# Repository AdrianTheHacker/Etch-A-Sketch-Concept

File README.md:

# Etchasketch Concept
This project is designed to be a concept of what an etchasketch could be. It'll allow for modern features that aid artist ability, and truly allow them to *Draw the Future*.

## Requirements
In no particular order, the requirements are as follows:
1. Display has at least 3 colours (white counts as a colour).
2. Display can update at least once per second.
3. Users can control the drawing cursor of the display using rotary inputs which read input a minimum of every 10ms*.
4. The product should be at most 77mm by 100mm by 40mm.
5. Users can save the current drawing on the display on a laptop.
6. Different devices can share a given drawing session to collaborate on designs.

*Note that the rate in which an input is processed is independent of the rate in which the screen will be updating.

## Specifications
* [1] E-Ink display capable of displaying 3 different colours.
* [1] Single button for cycling between colours.
* [2] E-Ink screen uses effective partial updating algorithm for reducing.
* [3] Two potentiometers for reading user inputs.
* [4] PCB has width of 100mm and length of 77mm.
* [5/6] PCB contains a [pre-certified WiFi module](https://www.adafruit.com/product/4201).
* [5/6] Desktop app for managing drawing sessions and saving drawing state.

## Component Selection
Sorted by sub-system.

### Processing
[STM32G4 Hardware Configuration](https://www.st.com/resource/en/application_note/an5093-getting-started-with-stm32g4-series--hardware-development-boards-stmicroelectronics.pdf)
- [2x] [Ceramic capacitor 100nF](https://www.mouser.ca/ProductDetail/TAIYO-YUDEN/MAJCH168BB7104KTEA01?qs=ZcfC38r4PovaTBrG0IdezQ%3D%3D)
- [1x] [Ceramic capacitor 4.7uF](https://www.mouser.ca/ProductDetail/TAIYO-YUDEN/LMK107BJ475KA-T?qs=PzICbMaShUfCoRlxZeLF0g%3D%3D)
- [3x] [Ceramic capacitor 1uF (No CAD Found)](https://www.mouser.ca/ProductDetail/Murata-Electronics/GCM188M8EH105KE08D?qs=ZcfC38r4Posf7JVKT9w1zw%3D%3D)
- [1x] [Ceramic capacitor 10nF](https://www.mouser.ca/ProductDetail/KYOCERA-AVX/06035A103JAT2A?qs=Cw3yY7soYCOJ7MBOLgA8ng%3D%3D)
- [2x] [Ceramic capacitor 6.8pF (No CAD Found)](https://www.mouser.ca/ProductDetail/KYOCERA-AVX/0603YA6R8CAT2A?qs=Q0wCMCRSJ1u%252BWh5kh2d1zQ%3D%3D)
- [2x] [Ceramic capacitor 20pF](https://www.mouser.ca/ProductDetail/KYOCERA-AVX/06031A200KAT2A?qs=vKkcnSRGkVsINiHJTia7rw%3D%3D)
- [1x] [Ferrite beads (No CAD Found)](https://www.mouser.ca/ProductDetail/TE-Connectivity-Sigma-Inductors/BMC-Q1E0000H?qs=IKkN%2F947nfDSkH2nnTPyEw%3D%3D)
- [1x] [Quartz 24MHz (No CAD Found)](https://www.mouser.ca/ProductDetail/KYOCERA-AVX/CX3225FB24000C0FZZH1?qs=Tc%252BHE9vUsnugTp3oEWKKRg%3D%3D)
- [1x] [Quartz 32.764kHz](https://www.mouser.ca/ProductDetail/Vishay-Dale/XT1312HHRXX32K76E?qs=jcD%2FCkGBYeMqyUz9UpSqCw%3D%3D)
- [1x] [Resistor 390Ω](https://www.mouser.ca/ProductDetail/Vishay-Beyschlag/MCT0603MD3900BP500?qs=sGAEpiMZZMtlubZbdhIBIONtIqra%2FA5Yq8ULjaRtKpA%3D)
- [3x] [Resistor 10kΩ](https://www.mouser.ca/ProductDetail/TE-Connectivity-Holsworthy/RA73F1J10KBTDF?qs=sGAEpiMZZMtlubZbdhIBIJBDgjsVQBFl0L0uqFOGEF8%3D)
- [1x] [ST-Link Debugger (STLINK-V3MINIE)](https://www.mouser.ca/ProductDetail/STMicroelectronics/STLINK-V3MINIE?qs=sGAEpiMZZMuqBwn8WqcFUipNgoezRlc4V9M2rz8Us%252BfpLfxQapoDpA%3D%3D)
- [1x] [ST-Link debugger connector (LibraryLoader didn't work)](https://www.digikey.ca/en/products/detail/samtec-inc/FTSH-107-01-F-DV-K/2650001?gclsrc=aw.ds&gad_source=1&gad_campaignid=17336435733&gbraid=0AAAAADrbLlhq2OpxPLWAyTiYmFA62M8dN&gclid=CjwKCAiAuIDJBhBoEiwAxhgyFisN6L1oPr3EJV2HRn68eJmM_TwOISw0mEKeCH2g0jNCqzJe0RDupRoCn4cQAvD_BwE)
- [1x] [STM32G484QET6](https://www.mouser.ca/ProductDetail/STMicroelectronics/STM32G484QET6?qs=uwxL4vQweFOef65amZQ%252BrA%3D%3D)
- [1x] [Switch (No CAD Found)](https://mou.sr/4ixqZ2V)
- [1x] [Pushbutton](https://www.mouser.ca/ProductDetail/CK/PTS125SM73SMTR21M-LFS?qs=t7xnP681wgVp4NpaUUvA%252Bw%3D%3D)

### Power
- [1x] [CR2032 Battery](https://www.mouser.ca/ProductDetail/Murata-Electronics/CR2032?qs=gTYE2QTfZfQ%2FQrgScp89FQ%3D%3D)
- [1x] [CR2032 Connector](https://www.mouser.ca/ProductDetail/Renata/SMTU2032-C?qs=UxeAxwACbqkmlMDdDbz%2FoA%3D%3D)
- [1x] [Power on LED Green](https://www.mouser.ca/ProductDetail/ams-OSRAM/KT-EELP41.12-S2U1-25-2X4X-5-R18?qs=sGAEpiMZZMvVL5Kk7ZYykaXDR74jB6yftoFsk4g727SHxqbUeiiZww%3D%3D)
- [1x] [Resistor 100Ω (for LED) (No CAD Found, Not Requested)](https://www.mouser.ca/ProductDetail/TE-Connectivity-Holsworthy/RT73F1J100RBTD?qs=sGAEpiMZZMtlubZbdhIBIOStsStSd9IEZF4WybNbkN0%3D)
- [1x] [Ceramic capacitor 10uF](https://www.mouser.ca/ProductDetail/KYOCERA-AVX/0603YD106MAT2A?qs=%252BdQmOuGyFcGTGabFXpuZrg%3D%3D)

### Display
[Screen's circuit diagram (Make manually)](https://cdn-shop.adafruit.com/product-files/6393/P6393+C22273-001_datasheet_ZJY296152-0266EABMFGN-R.pdf)
- [1x] [E-Ink display tri-colour 2.66In diagonal](https://www.adafruit.com/product/6393)
- [9x] [Ceramic capacitor 1uF](https://www.mouser.ca/ProductDetail/TAIYO-YUDEN/MAJCT168BB7105KTEA01?qs=ZcfC38r4PotKRnvquyYkSA%3D%3D)
- [1x] [Resistor 2.2Ω (No CAD Found, Not Requested)](https://www.mouser.ca/ProductDetail/Wurth-Elektronik/560112116088?qs=mELouGlnn3eIPFCFgc7e7A%3D%3D)
- [3x] [Diode](https://www.mouser.ca/ProductDetail/onsemi/MBR0530T1G?qs=3JMERSakeboS%2FFOxJUMWeg%3D%3D)
- [1x] [NMOS](https://www.mouser.ca/ProductDetail/Nexperia/NX3008NBKS115?qs=N31o%252Bt096gvSMWdFEcaa8A%3D%3D)
- [1x] [Inductor 47uH (No CAD Found, Not Requested)](https://www.mouser.ca/ProductDetail/Sumida/CDRH2D18-LDNP-470NC?qs=mT6umqgwvA1P4peHEoEcxg%3D%3D)
- [1x] [Screen connector (Downloaded, Add Manually)](https://www.digikey.ca/en/products/detail/w%C3%BCrth-elektronik/687124149022/5047796)

### Controls
- [1x] [Accelerometer](https://www.mouser.ca/ProductDetail/Analog-Devices/ADXL345BCCZ?qs=WIvQP4zGanhoa7YOkGtvEg%3D%3D)
- [1x] [Ceramic capacitor 100nF](https://www.mouser.ca/ProductDetail/TAIYO-YUDEN/MAJCH168BB7104KTEA01?qs=ZcfC38r4PovaTBrG0IdezQ%3D%3D)
- [1x] [Tantalum capacitor 1uF](https://www.mouser.ca/ProductDetail/KYOCERA-AVX/TACL105K010FTA?qs=sGAEpiMZZMtZ1n0r9vR22f0Jgorj1M1u11EugVUWwzY%3D)
- [2x] [Potentiometer 10KΩ (Create Manually)](https://www.adafruit.com/product/3395)
- [2x] [Potentiometer cap](https://www.adafruit.com/product/2057)
- [2x] [Pushbutton](https://www.mouser.ca/ProductDetail/CK/PTS125SM73SMTR21M-LFS?qs=t7xnP681wgVp4NpaUUvA%252Bw%3D%3D)
- [2x] [Resistor 10kΩ](https://www.mouser.ca/ProductDetail/TE-Connectivity-Holsworthy/RA73F1J10KBTDF?qs=sGAEpiMZZMtlubZbdhIBIJBDgjsVQBFl0L0uqFOGEF8%3D)

### Connectivity
- [1x] [WiFi Module (Make Manually, Base off of pin headers)](https://www.adafruit.com/product/4201)
- [3x] [Pin header (Sets of 4)](https://www.mouser.ca/ProductDetail/HARTING/14120416050000?qs=sGAEpiMZZMvlX3nhDDO4ADo1TeYw%2F5hz1M8q0I2khik%3D)

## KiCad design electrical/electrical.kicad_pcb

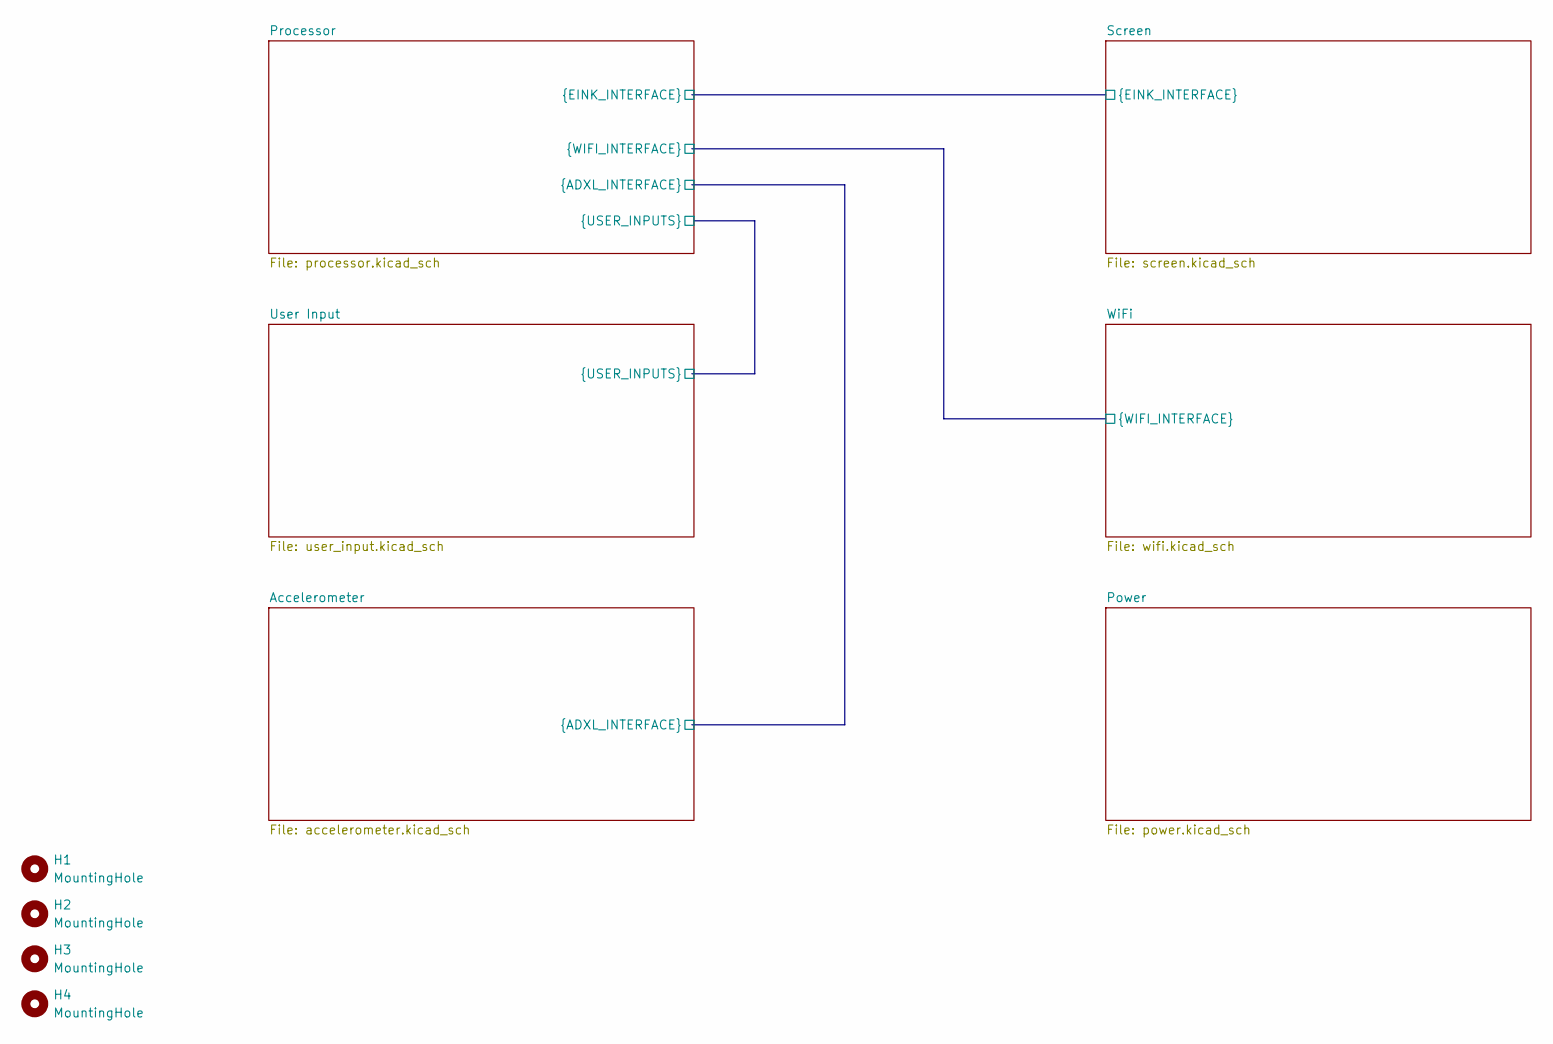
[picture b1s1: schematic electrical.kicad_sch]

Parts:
H1, H2, H3, H4: MountingHole; MountingHole_2.2mm_M2

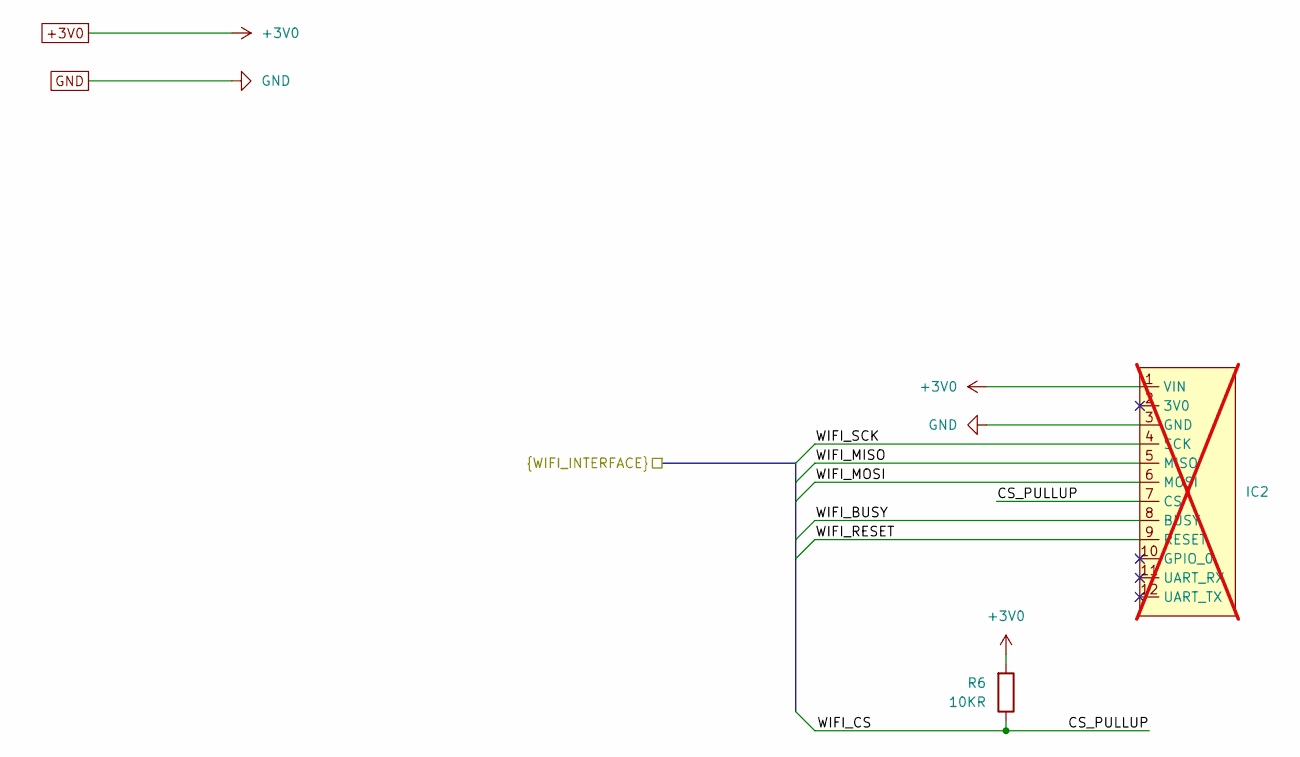
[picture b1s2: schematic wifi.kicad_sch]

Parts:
IC2: THT_WIFI_MODULE; not fitted
R6: 10KR; SMD_RESISTOR_0603

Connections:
+3V0: IC2.1 (VIN), R6.2; also elsewhere on the board
/Processor/WIFI_BUSY: IC2.8 (BUSY); also elsewhere on the board
/Processor/WIFI_CS: IC2.7 (CS), R6.1; also elsewhere on the board
/Processor/WIFI_MISO: IC2.5 (MISO); also elsewhere on the board
/Processor/WIFI_MOSI: IC2.6 (MOSI); also elsewhere on the board
/Processor/WIFI_RESET: IC2.9 (RESET); also elsewhere on the board
/Processor/WIFI_SCK: IC2.4 (SCK); also elsewhere on the board
GND: IC2.3 (GND); also elsewhere on the board

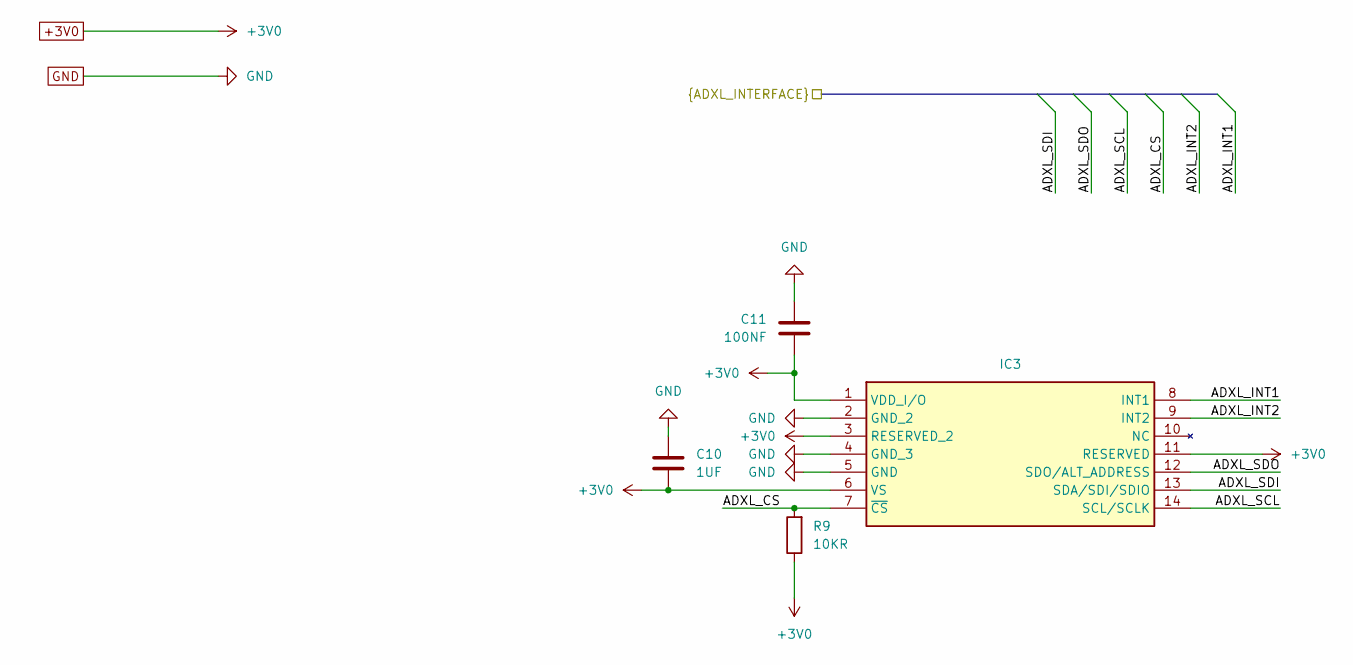
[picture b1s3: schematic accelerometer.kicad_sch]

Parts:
C10: 1UF; SMD_CAPACITOR_TANTALUM_0603_1UF
C11: 100NF; SMD_CAPACITOR_CERAMIC_0603
IC3: SMD_ADXL345BCCZ
R9: 10KR; SMD_RESISTOR_0603

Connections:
+3V0: C10.2, C11.1, IC3.1 (VDD_I/O), IC3.3 (RESERVED_2), IC3.6 (VS), IC3.11 (RESERVED), R9.1; also elsewhere on the board
/Accelerometer/ADXL_CS: IC3.7 (~CS), R9.2; also elsewhere on the board
/Accelerometer/ADXL_INT1: IC3.8 (INT1); also elsewhere on the board
/Accelerometer/ADXL_INT2: IC3.9 (INT2); also elsewhere on the board
/Accelerometer/ADXL_SCL: IC3.14 (SCL/SCLK); also elsewhere on the board
/Accelerometer/ADXL_SDI: IC3.13 (SDA/SDI/SDIO); also elsewhere on the board
/Accelerometer/ADXL_SDO: IC3.12 (SDO/ALT_ADDRESS); also elsewhere on the board
GND: C10.1, C11.2, IC3.2 (GND_2), IC3.4 (GND_3), IC3.5 (GND); also elsewhere on the board

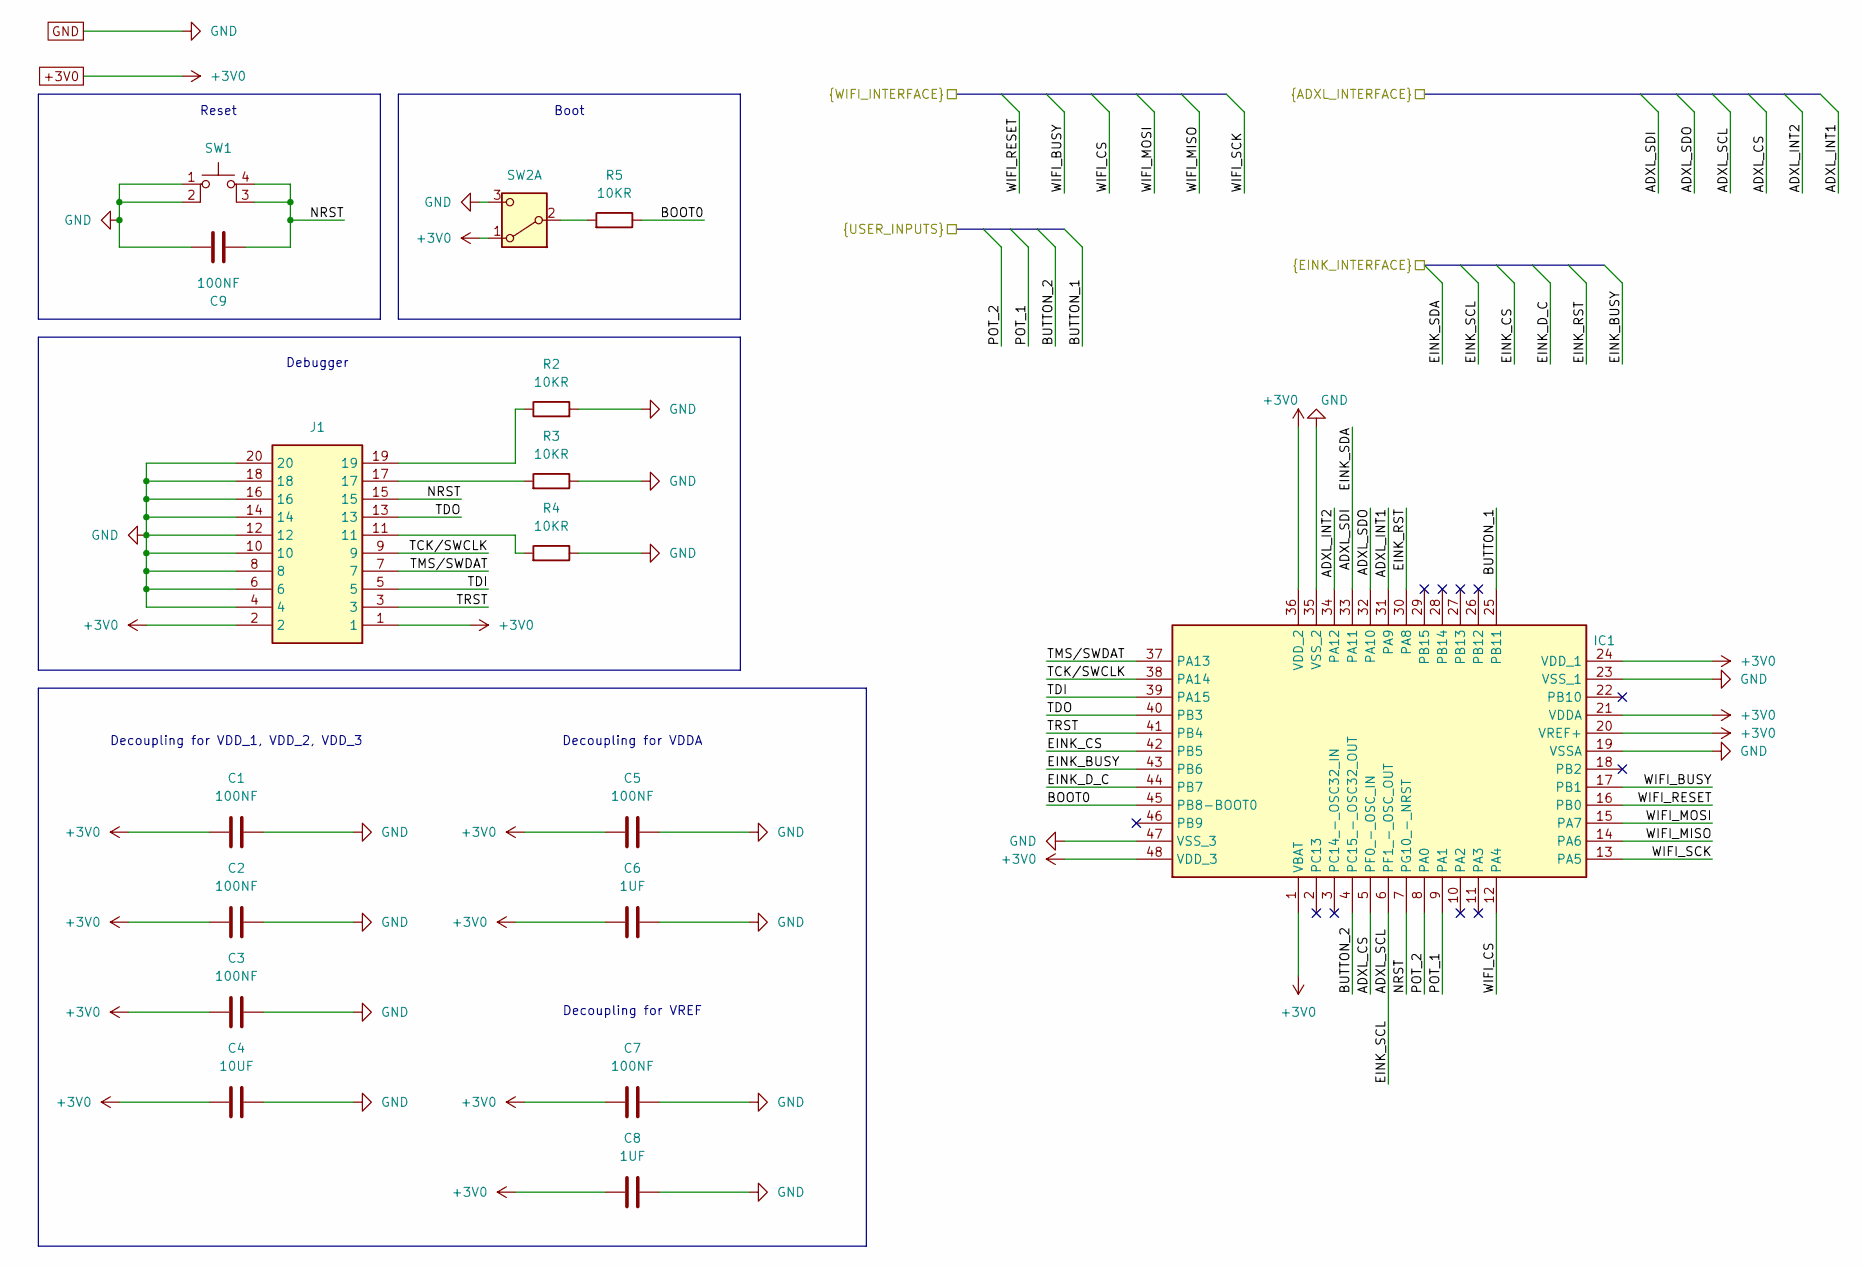
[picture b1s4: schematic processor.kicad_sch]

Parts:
C1, C2, C3, C5, C7, C9: 100NF; SMD_CAPACITOR_CERAMIC_0603
C4: 10UF; SMD_CAPACITOR_CERAMIC_0603
C6, C8: 1UF; SMD_CAPACITOR_CERAMIC_0603
IC1: STM32G474CBT6TR; SMD_STM32G474CBT6TR
J1: 24 Pins; THT_CONNECTOR_JTAG_SWD
R2, R3, R4, R5: 10KR; SMD_RESISTOR_0603
SW1: SMD_BUTTON
SW2: SMD_SWITCH_HORIZONTAL

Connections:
+3V0: C1.2, C2.2, C3.2, C4.1, C5.2, C6.1, C7.2, C8.1, IC1.1 (VBAT), IC1.20 (VREF+), IC1.21 (VDDA), IC1.24 (VDD_1), IC1.36 (VDD_2), IC1.48 (VDD_3), J1.1, J1.2, SW2.1 (A); also elsewhere on the board
/Accelerometer/ADXL_CS: IC1.5 (PF0_-_OSC_IN); also elsewhere on the board
/Accelerometer/ADXL_INT1: IC1.31 (PA9); also elsewhere on the board
/Accelerometer/ADXL_INT2: IC1.34 (PA12); also elsewhere on the board
/Accelerometer/ADXL_SCL: IC1.6 (PF1_-_OSC_OUT); also elsewhere on the board
/Accelerometer/ADXL_SDI: IC1.33 (PA11); also elsewhere on the board
/Accelerometer/ADXL_SDO: IC1.32 (PA10); also elsewhere on the board
/Processor/BOOT0: IC1.45 (PB8-BOOT0), R5.1
/Processor/BUTTON_1: IC1.25 (PB11); also elsewhere on the board
/Processor/BUTTON_2: IC1.4 (PC15_-_OSC32_OUT); also elsewhere on the board
/Processor/EINK_BUSY: IC1.43 (PB6); also elsewhere on the board
/Processor/EINK_CS: IC1.42 (PB5); also elsewhere on the board
/Processor/EINK_D_C: IC1.44 (PB7); also elsewhere on the board
/Processor/EINK_RST: IC1.30 (PA8); also elsewhere on the board
/Processor/NRST: C9.1, IC1.7 (PG10_-_NRST), J1.15, SW1.3 (K), SW1.4 (A)
/Processor/POT_1: IC1.9 (PA1); also elsewhere on the board
/Processor/POT_2: IC1.8 (PA0); also elsewhere on the board
/Processor/TCK/SWCLK: IC1.38 (PA14), J1.9
/Processor/TDI: IC1.39 (PA15), J1.5
/Processor/TDO: IC1.40 (PB3), J1.13
/Processor/TMS/SWDAT: IC1.37 (PA13), J1.7
/Processor/TRST: IC1.41 (PB4), J1.3
/Processor/WIFI_BUSY: IC1.17 (PB1); also elsewhere on the board
/Processor/WIFI_CS: IC1.12 (PA4); also elsewhere on the board
/Processor/WIFI_MISO: IC1.14 (PA6); also elsewhere on the board
/Processor/WIFI_MOSI: IC1.15 (PA7); also elsewhere on the board
/Processor/WIFI_RESET: IC1.16 (PB0); also elsewhere on the board
/Processor/WIFI_SCK: IC1.13 (PA5); also elsewhere on the board
GND: C1.1, C2.1, C3.1, C4.2, C5.1, C6.2, C7.1, C8.2, C9.2, IC1.19 (VSSA), IC1.23 (VSS_1), IC1.35 (VSS_2), IC1.47 (VSS_3), J1.4, J1.6, J1.8, J1.10, J1.12, J1.14, J1.16, J1.18, J1.20, R2.2, R3.1, R4.1, SW1.1, SW1.2, SW2.3 (C); also elsewhere on the board
unnamed: J1.11, R4.2
unnamed: J1.17, R3.2
unnamed: J1.19, R2.1
unnamed: R5.2, SW2.2 (B)

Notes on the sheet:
Debugger
Reset
Boot
Decoupling for VDDA
Decoupling for VDD_1, VDD_2, VDD_3
Decoupling for VREF

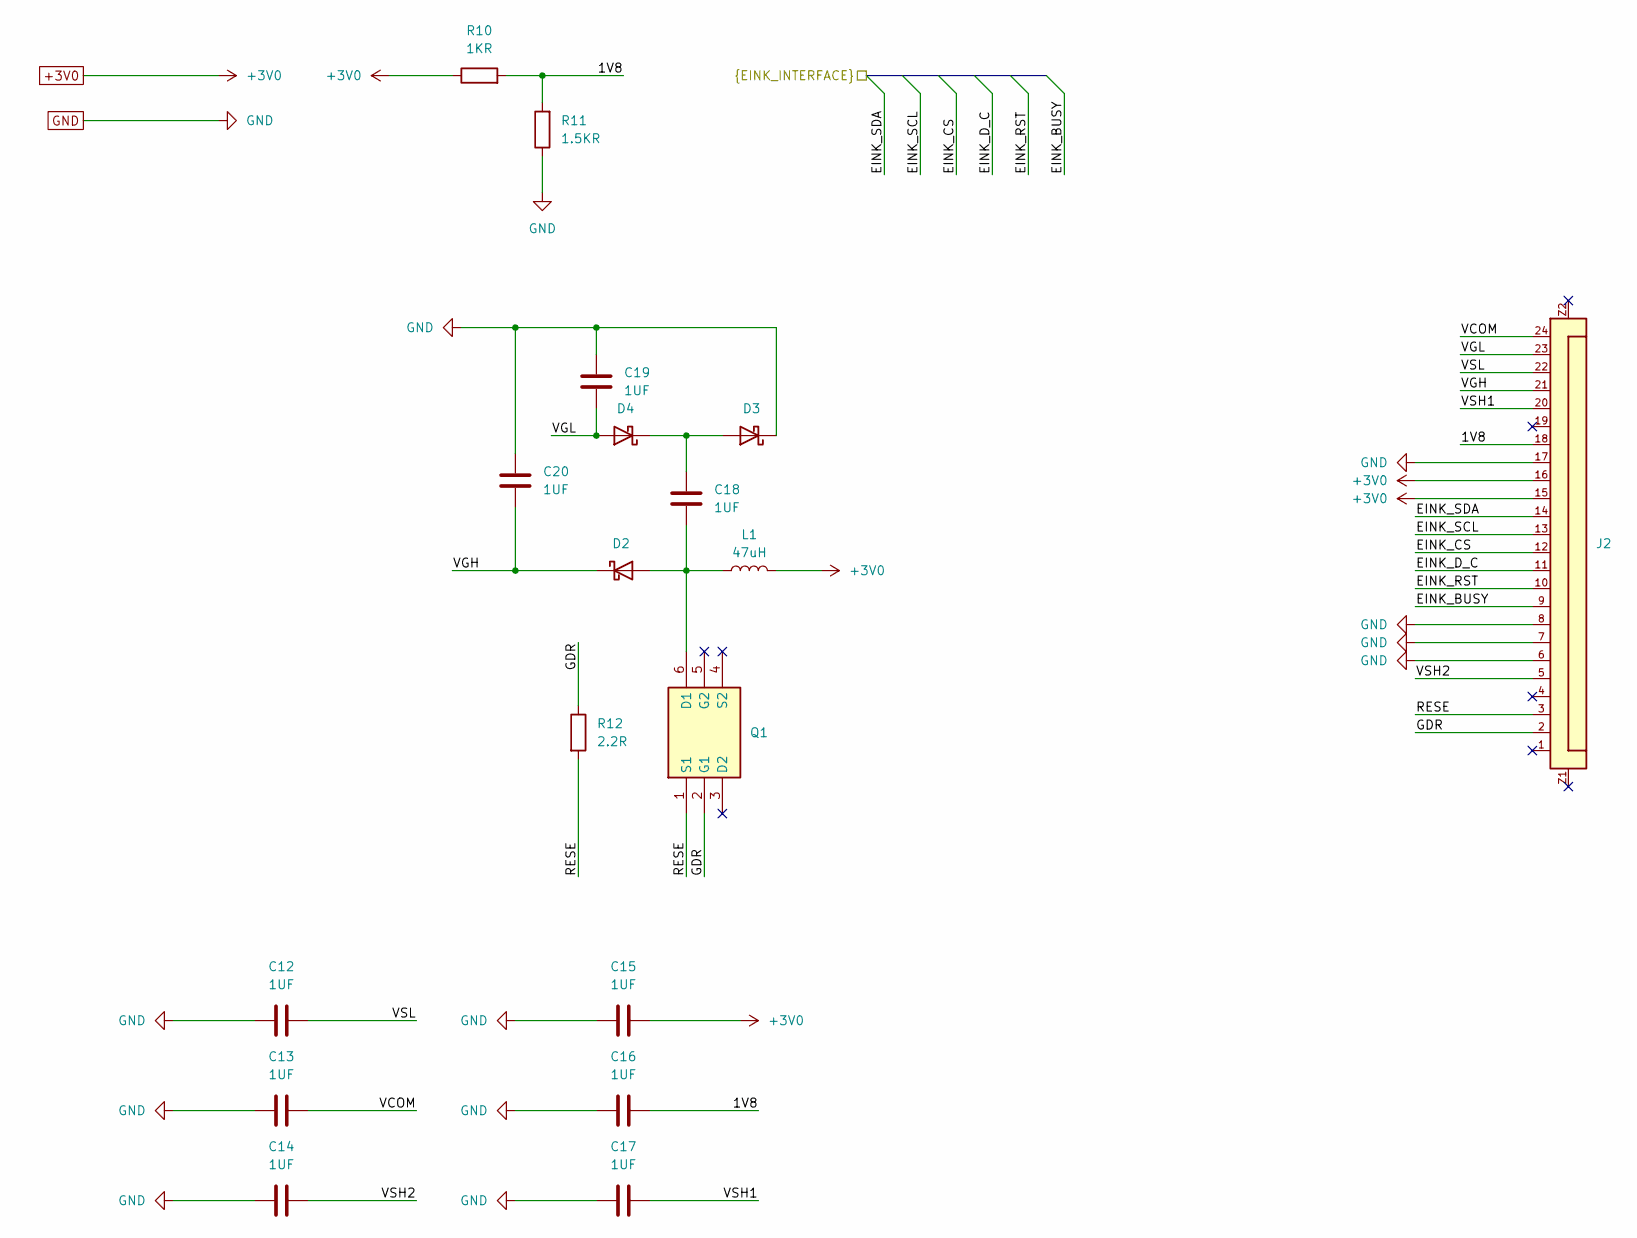
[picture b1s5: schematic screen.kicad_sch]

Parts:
C12, C13, C14, C15, C16, C17, C18, C19, C20: 1UF; SMD_CAPACITOR_CERAMIC_0603
D2, D3, D4: SMD_DIODE_MBR0530T1G
J2: 6871XX149022_687124149022; SMD_CONNECTOR_RIBBON_CABLE_24_PINS
L1: 47uH; SMD_INDUCTOR_0603
Q1: SMD_MOSFET_NX3008NBKS
R10: 1KR; SMD_RESISTOR_0603
R11: 1.5KR; SMD_RESISTOR_0603
R12: 2.2R; SMD_RESISTOR_0603

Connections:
+3V0: C15.2, J2.15, J2.16, L1.2, R10.1; also elsewhere on the board
/Accelerometer/ADXL_SCL: J2.13; also elsewhere on the board
/Accelerometer/ADXL_SDI: J2.14; also elsewhere on the board
/Processor/EINK_BUSY: J2.9; also elsewhere on the board
/Processor/EINK_CS: J2.12; also elsewhere on the board
/Processor/EINK_D_C: J2.11; also elsewhere on the board
/Processor/EINK_RST: J2.10; also elsewhere on the board
/Screen/1V8: C16.2, J2.18, R10.2, R11.2
/Screen/GDR: J2.2, Q1.2 (G1), R12.2
/Screen/RESE: J2.3, Q1.1 (S1), R12.1
/Screen/VCOM: C13.1, J2.24
/Screen/VGH: C20.2, D2.1 (K), J2.21
/Screen/VGL: C19.1, D4.2 (A), J2.23
/Screen/VSH1: C17.2, J2.20
/Screen/VSH2: C14.2, J2.5
/Screen/VSL: C12.1, J2.22
GND: C12.2, C13.2, C14.1, C15.1, C16.1, C17.1, C19.2, C20.1, D3.1 (K), J2.6, J2.7, J2.8, J2.17, R11.1; also elsewhere on the board
unnamed: C18.1, D2.2 (A), L1.1, Q1.6 (D1)
unnamed: C18.2, D3.2 (A), D4.1 (K)

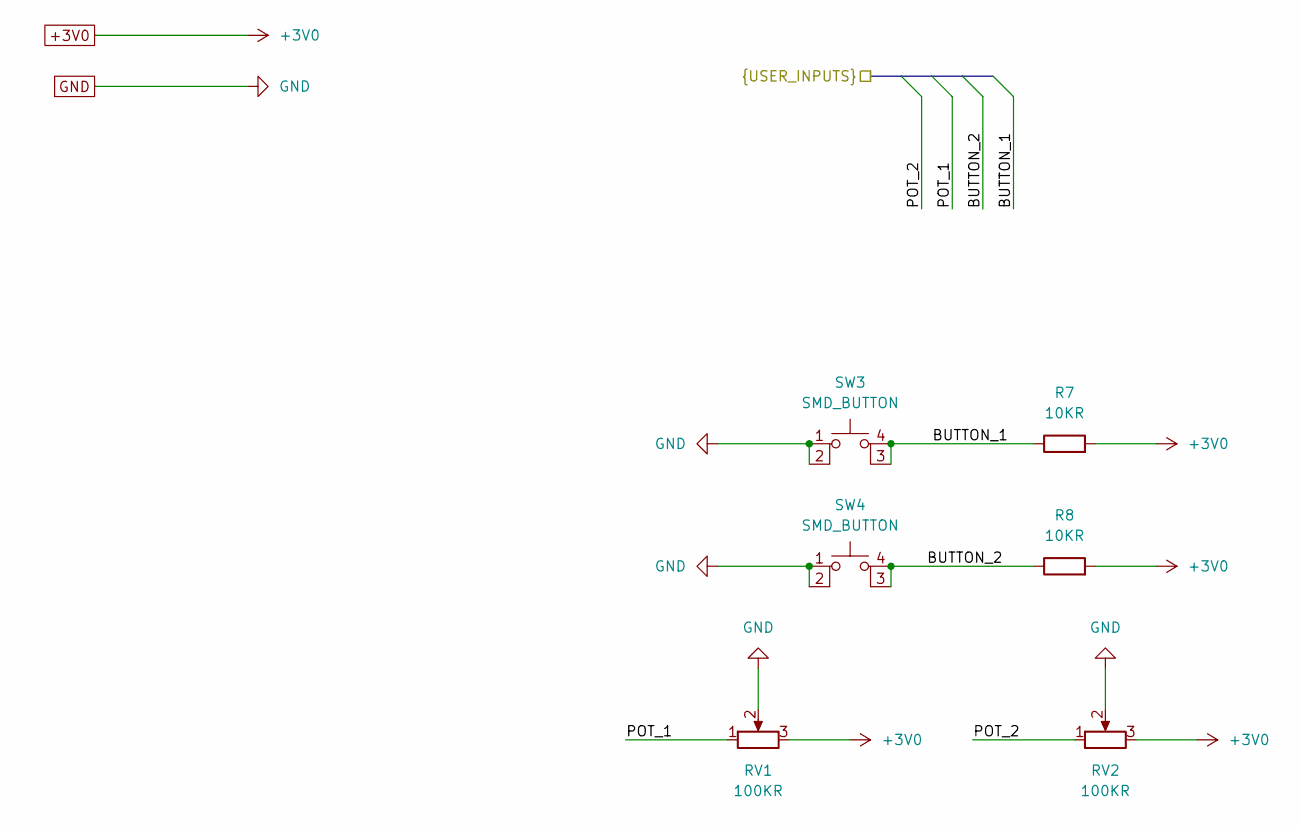
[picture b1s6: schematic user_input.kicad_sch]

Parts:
R7, R8: 10KR; SMD_RESISTOR_0603
RV1, RV2: 100KR; THT_POTENTIOMETER_100KR
SW3, SW4: SMD_BUTTON

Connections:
+3V0: R7.2, R8.2, RV1.3, RV2.3; also elsewhere on the board
/Processor/BUTTON_1: R7.1, SW3.3 (K), SW3.4 (A); also elsewhere on the board
/Processor/BUTTON_2: R8.1, SW4.3 (K), SW4.4 (A); also elsewhere on the board
/Processor/POT_1: RV1.1; also elsewhere on the board
/Processor/POT_2: RV2.1; also elsewhere on the board
GND: RV1.2, RV2.2, SW3.1, SW3.2, SW4.1, SW4.2; also elsewhere on the board

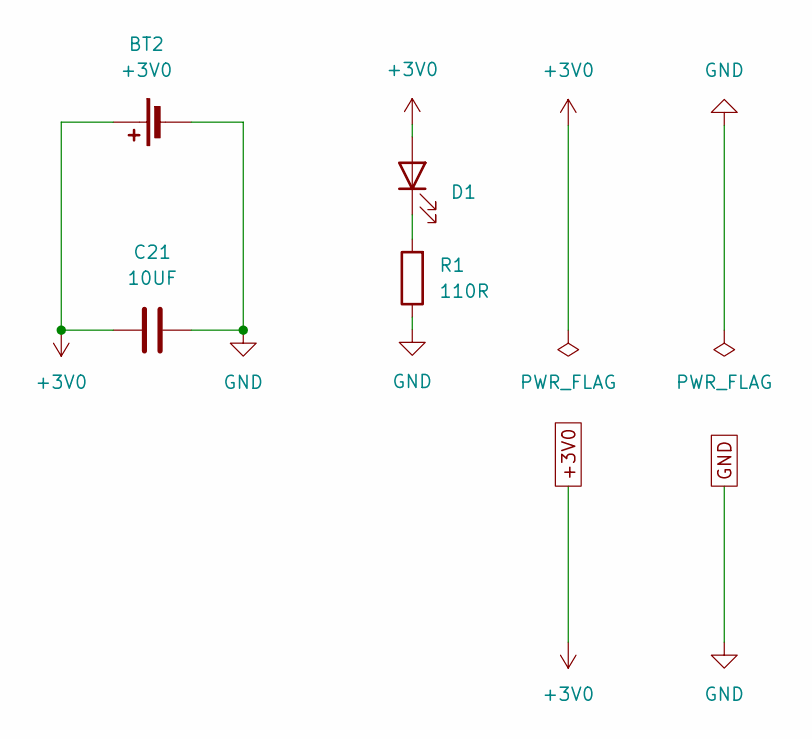
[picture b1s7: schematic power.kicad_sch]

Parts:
BT2: +3V0; SMD_BATTERY_SINGLE_CELL_CR2032
C21: 10UF; SMD_CAPACITOR_CERAMIC_0603
D1: Green; SMD_LED_GREEN_0603
R1: 110R; SMD_RESISTOR_0603

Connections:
+3V0: BT2.1 (+), C21.1, D1.2 (A); also elsewhere on the board
GND: BT2.2 (-), C21.2, R1.1; also elsewhere on the board
unnamed: D1.1 (K), R1.2

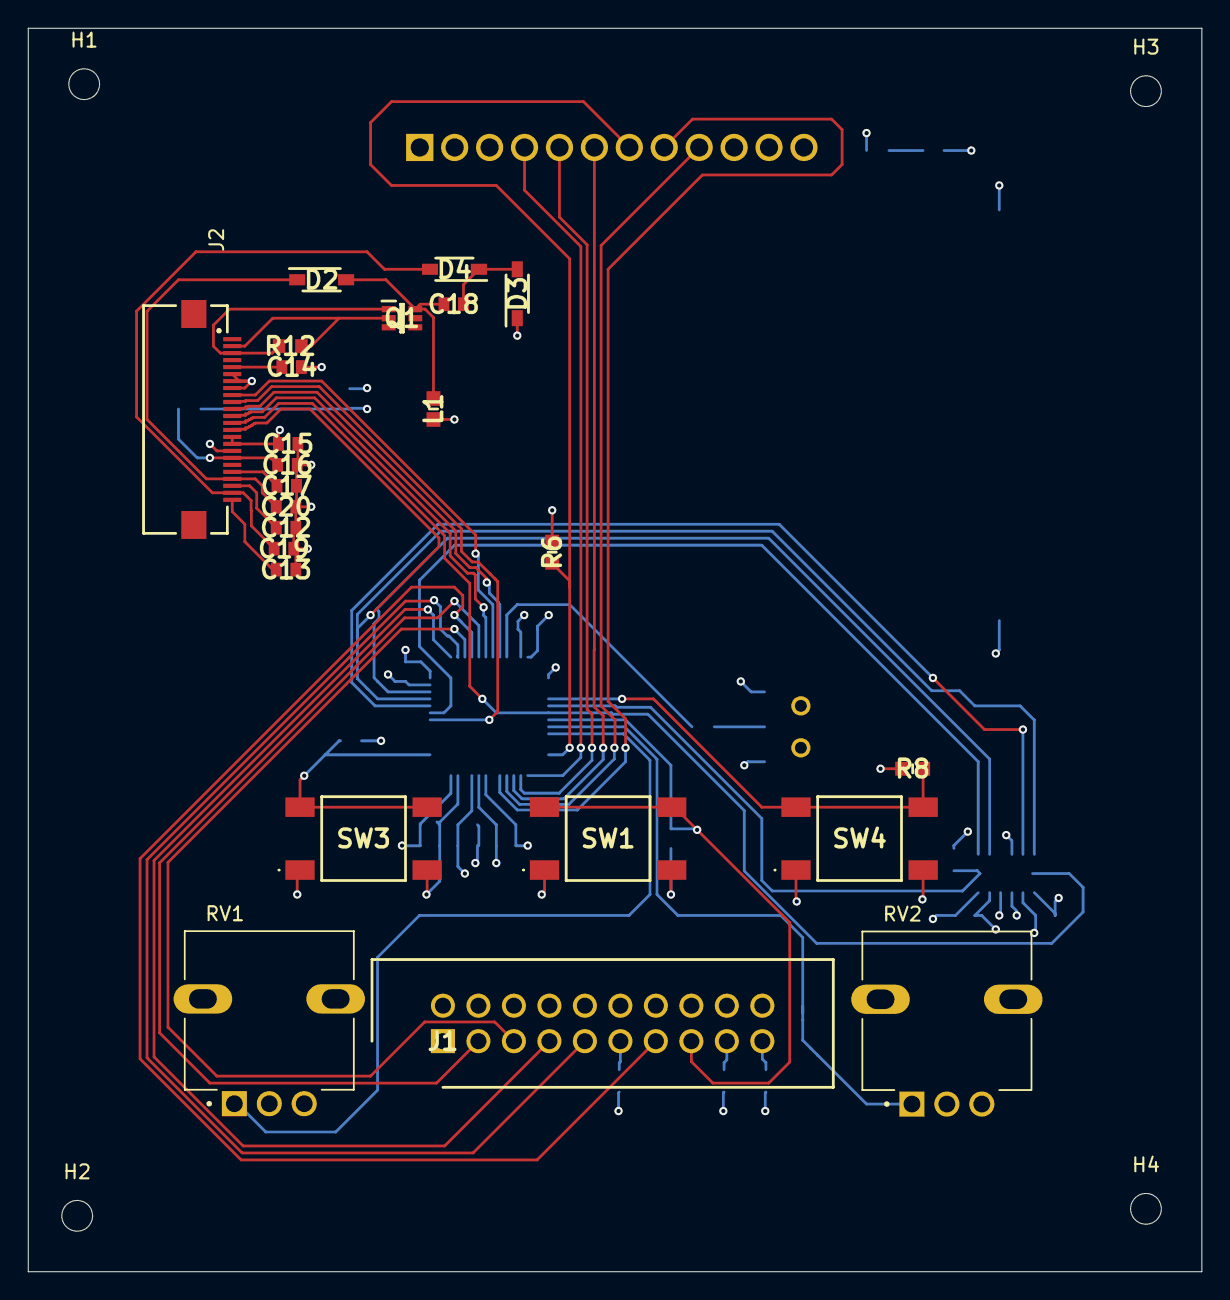
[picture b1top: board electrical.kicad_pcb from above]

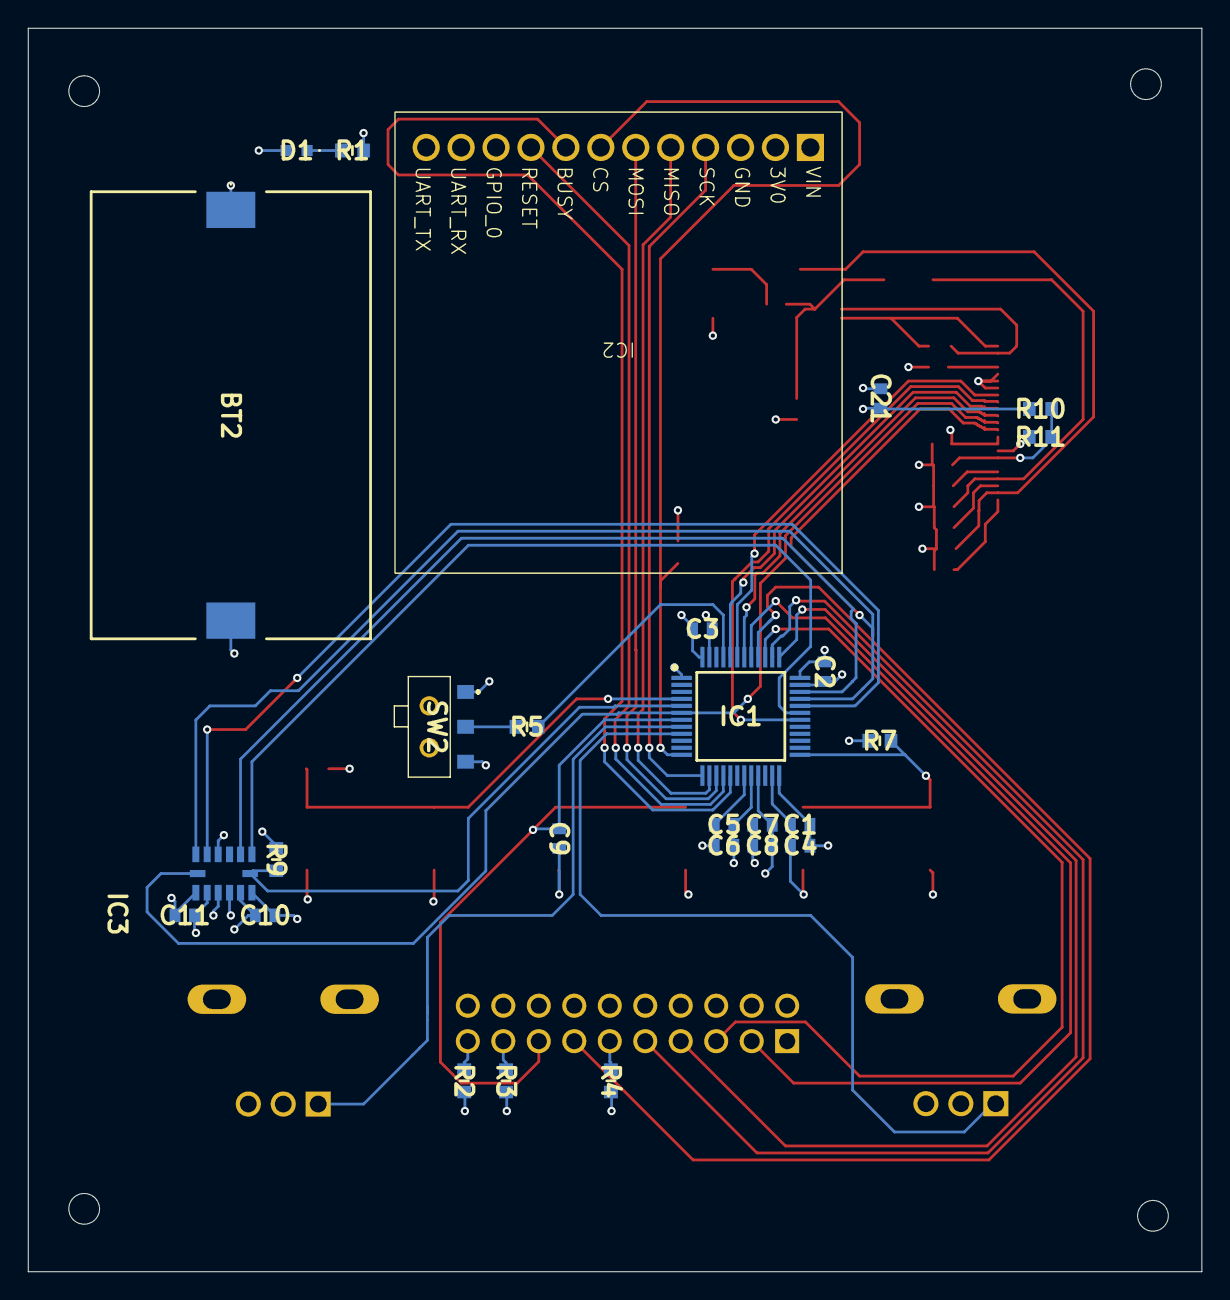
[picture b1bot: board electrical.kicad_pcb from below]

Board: 4 copper layers, 84.0 x 89.0 mm, 55 parts (27 on the bottom side), 45 nets.

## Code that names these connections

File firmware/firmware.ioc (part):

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Mcu.Name=STM32G474C(B-C-E)Tx
Mcu.Package=LQFP48
Mcu.UserName=STM32G474CBTx
PA0.GPIOParameters=GPIO_Label
PA0.GPIO_Label=POT_2
PA0.Mode=IN1-Single-Ended
PA0.Signal=ADC2_IN1
PA1.GPIOParameters=GPIO_Label
PA1.GPIO_Label=POT_1
PA1.Mode=IN2-Single-Ended
PA1.Signal=ADC1_IN2
PA10.GPIOParameters=GPIO_Label
PA10.GPIO_Label=ADXL_EINK_MISO
PA10.Mode=Full_Duplex_Master
PA10.Signal=SPI2_MISO
PA11.GPIOParameters=GPIO_Label
PA11.GPIO_Label=ADXL_EINK_MOSI
PA11.Mode=Full_Duplex_Master
PA11.Signal=SPI2_MOSI
PA12.GPIOParameters=GPIO_Label
PA12.GPIO_Label=ADXL_INT2
PA12.Signal=GPIO_Input
PA2.GPIOParameters=GPIO_Label
PA2.GPIO_Label=BUTTON_1
PA2.Signal=GPIO_Input
PA4.GPIOParameters=GPIO_Label
PA4.GPIO_Label=WIFI_CS
PA4.Mode=NSS_Signal_Hard_Output
PA4.Signal=SPI1_NSS
PA5.GPIOParameters=GPIO_Label
PA5.GPIO_Label=WIFI_SCK
PA5.Mode=Full_Duplex_Master
PA5.Signal=SPI1_SCK
PA6.GPIOParameters=GPIO_Label
PA6.GPIO_Label=WIFI_MISO
PA6.Mode=Full_Duplex_Master
PA6.Signal=SPI1_MISO
PA7.GPIOParameters=GPIO_Label
PA7.GPIO_Label=WIFI_MOSI
PA7.Mode=Full_Duplex_Master
PA7.Signal=SPI1_MOSI
PA8.GPIOParameters=GPIO_Label
PA8.GPIO_Label=EINK_RST
PA8.Signal=GPIO_Output
PA9.GPIOParameters=GPIO_Label
PA9.GPIO_Label=ADXL_INT1
PA9.Signal=GPIO_Input
PB0.GPIOParameters=GPIO_Label
PB0.GPIO_Label=WIFI_RESET
PB0.Signal=GPIO_Output
PB1.GPIOParameters=GPIO_Label
PB1.GPIO_Label=WIFI_BUSY
PB1.Signal=GPIO_Input
PB5.GPIOParameters=GPIO_Label
PB5.GPIO_Label=EINK_CS
PB5.Signal=GPIO_Output
PB6.GPIOParameters=GPIO_Label
PB6.GPIO_Label=EINK_BUSY
PB6.Signal=GPIO_Input
PB7.GPIOParameters=GPIO_Label
PB7.GPIO_Label=EINK_D_C
PB7.Signal=GPIO_Output
PC15-OSC32_OUT.GPIOParameters=GPIO_Label
PC15-OSC32_OUT.GPIO_Label=BUTTON_2
PC15-OSC32_OUT.Signal=GPIO_Input
PF0-OSC_IN.GPIOParameters=GPIO_Label
PF0-OSC_IN.GPIO_Label=ADXL_CS
PF0-OSC_IN.Signal=GPIO_Output
PF1-OSC_OUT.GPIOParameters=GPIO_Label
PF1-OSC_OUT.GPIO_Label=ADXL_EINK_SCK
PF1-OSC_OUT.Mode=Full_Duplex_Master
PF1-OSC_OUT.Signal=SPI2_SCK
RCC.HSE_VALUE=8000000
RCC.SYSCLKFreq_VALUE=16000000
board=custom

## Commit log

2025-09-30 Updating project planning document.
2025-10-01 Updating optional features.
2025-10-07 Adding electrical stuff
2025-10-08 #3 Adding gitignore
2025-10-08 #3 Creating symbol library and symbol for E-Ink display.
2025-10-08 #3 Implementing symbol for coincell battery case and updating symbol datasheets and descriptions.
2025-10-08 #3 Improving the coincell battery holder symbol.
2025-10-08 #3 Connecting MCU connectors to E-Ink on schematic.
2025-10-08 #3 Creating symbol for accelerometer.
2025-10-11 #3 Updating system design.
2025-10-11 #3 Creating the system diagram.
2025-10-11 #3 Creating power sub-schematic.
2025-10-11 #3 Sourcing capacitors, and designing power for MCU.
2025-10-11 #3 Adding accelerometer to schematic.
2025-10-17 #3 Improving accelerometer schematic.
2025-10-17 #3 Adding footprints for capacitors.
2025-10-17 #3 Making symbols.
2025-10-17 #3 Finishing some circuitry.
2025-10-21 Making minor fixes to the schematic.
2025-10-22 Finishing schematic
2025-10-22 Completing schematic.
2025-10-22 Generating BOM.
2025-10-22 Updating firmware.
2025-10-22 Adding pots.
2025-11-07 #10 Updating the project's requirements.
2025-11-07 #10 Adding measurable units to requirements.
2025-11-07 Cleaning main.
2025-11-07 #12 Complete proejct specifications.
2025-11-22 #12 Defining project specifications.
2025-11-22 #14 Adding neccessary components for the processor
2025-11-22 #14 Adding STM32's docs on hardware configuration.
2025-11-22 #14 Adding all processing components.
2025-11-22 #14 Completing component selection for power
2025-11-22 #14 Adding rest of component selection.
2025-11-22 #19 Implementing top level sheets.
2025-11-22 #18 Adding decoupling capacitor.
2025-11-22 #3 Completing power section.
2025-11-22 #3 Making minor changes to power.
2025-11-23 #3 Implementing base schematic for processor.
2025-11-30 #3 Implementing potentionometers and beginning IOC file creation.
2025-11-30 #3 Adding controls connections to STM32, updating IOC file to match.
2025-11-30 #3 Adding WiFi module to the schematic.
2025-11-30 #3 Updating IOC file.
2025-12-01 #3 Updating schematic.
2025-12-04 #3 Finding CAD for switch.
2025-12-04 README.md
2025-12-04 #3 Adding stuff.
2025-12-04 not in working state yet.
2025-12-06 #17 Making layout. Errors rpesent.
2025-12-06 #17 Finish PCB layout.
2025-12-07 Uploading some work
2025-12-09 Adding gerbers.
2025-12-16 Making progress on schematic and developing IOC.
2025-12-16 Adding gitignore
2025-12-16 Adding user input.
2025-12-16 Adding decoupling capacitors for STM.
2025-12-16 Adding more to layout.
2025-12-17 Completing PCB layout.
2025-12-17 Adding stuff
2025-12-17 Adding more stuff
2025-12-18 Removing useles file.
2025-12-18 Adding build files.
2025-12-20 Improving manufacturability of the board.
2025-12-20 Adding more proejct files.
2026-01-05 Adding manufacturer and manufacturer number to path.
2026-01-10 Updating schematic pages.
